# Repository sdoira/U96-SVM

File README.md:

# U96-SVM
Stereo vision front-end for Ultra96v2

## About
U96-SVM is an add-on board for Avnet Ultra96v2.
This board has dual CMOS image sensors and two mikroBUS sites.
This repository contains all design files for the hardware and a sample project 
which transfers stereo images through a USB interface.

## Tools

These tools are used to create this project.
1. Avnet Ultra96v2
2. Autodesk EAGLE 9.6.2
3. Xilinx Vivado 2020.1
4. Xilinx Vitis 2020.1

## PCB
This PCB is designed to be compliant with 96Boards specifications.
The number of layers is 4.
The minimum trace width and minimum drill diameter are 0.15mm and 0.25mm respectively.
This design rule is according to EuroCircuits 6D class.

EAGLE 9.6.2 is used in designing PCB.
This project doesn't contain Gerber files. EAGLE board layout file (.brd) is directly used to order manufacturing.
If you want to place an order simply upload the BRD file to the EuroCircuits website.
The assembly service is also possible by enabling the "Include assembly" option then upload the BOM file.

## USB Interface
This device is recognized as USB Video Class (UVC) device when connected to the host PC.
The sample project supports the following resolution both for USB2.0 and USB3.0.

| USB Ver. | Single Image Resolution | FPS  |
| :---     | :---                    | :--- |
| 2.0      | 640 x 480               | 30   |
| 3.0      | 640 x 480               | 30   |

The left and right images are combined horizontally.
The actual output image is twice wide.

## Vivado Project
This repository contains 2 Vivado projects.
One of them is the Vivado top level project.
The other is a project for a user-created IP module.
Both of them can be created by running TCL scripts.
Refer to "create_project_dvp.pdf" and "create_project1.pdf" about how to create these projects.

## Vitis Project
The Vitis project contains a sample application named "usb_grabber".
This application, when launched, automatically starts DMA transferring of stereo images while waiting for a USB connection.
Refer to "create_vitis_project.pdf" about how to create the Vitis project.

## License
### Hardware
The hardware documentation and products included in this repository are licensed under the TAPR Open Hardware License (www.tapr.org/OHL).
The hardware documentation is contained in the following directory.

	/eagle/

### Software
The software design files included in this repository are available under the MIT license.
Such design files are contained in the following directories.

	/src/dvp/rtl/		--- Verilog-HDL RTL source
	/src/dvp/sim/		--- Verilog-HDL simulation test bench
	/src/usb_grabber/	--- C source

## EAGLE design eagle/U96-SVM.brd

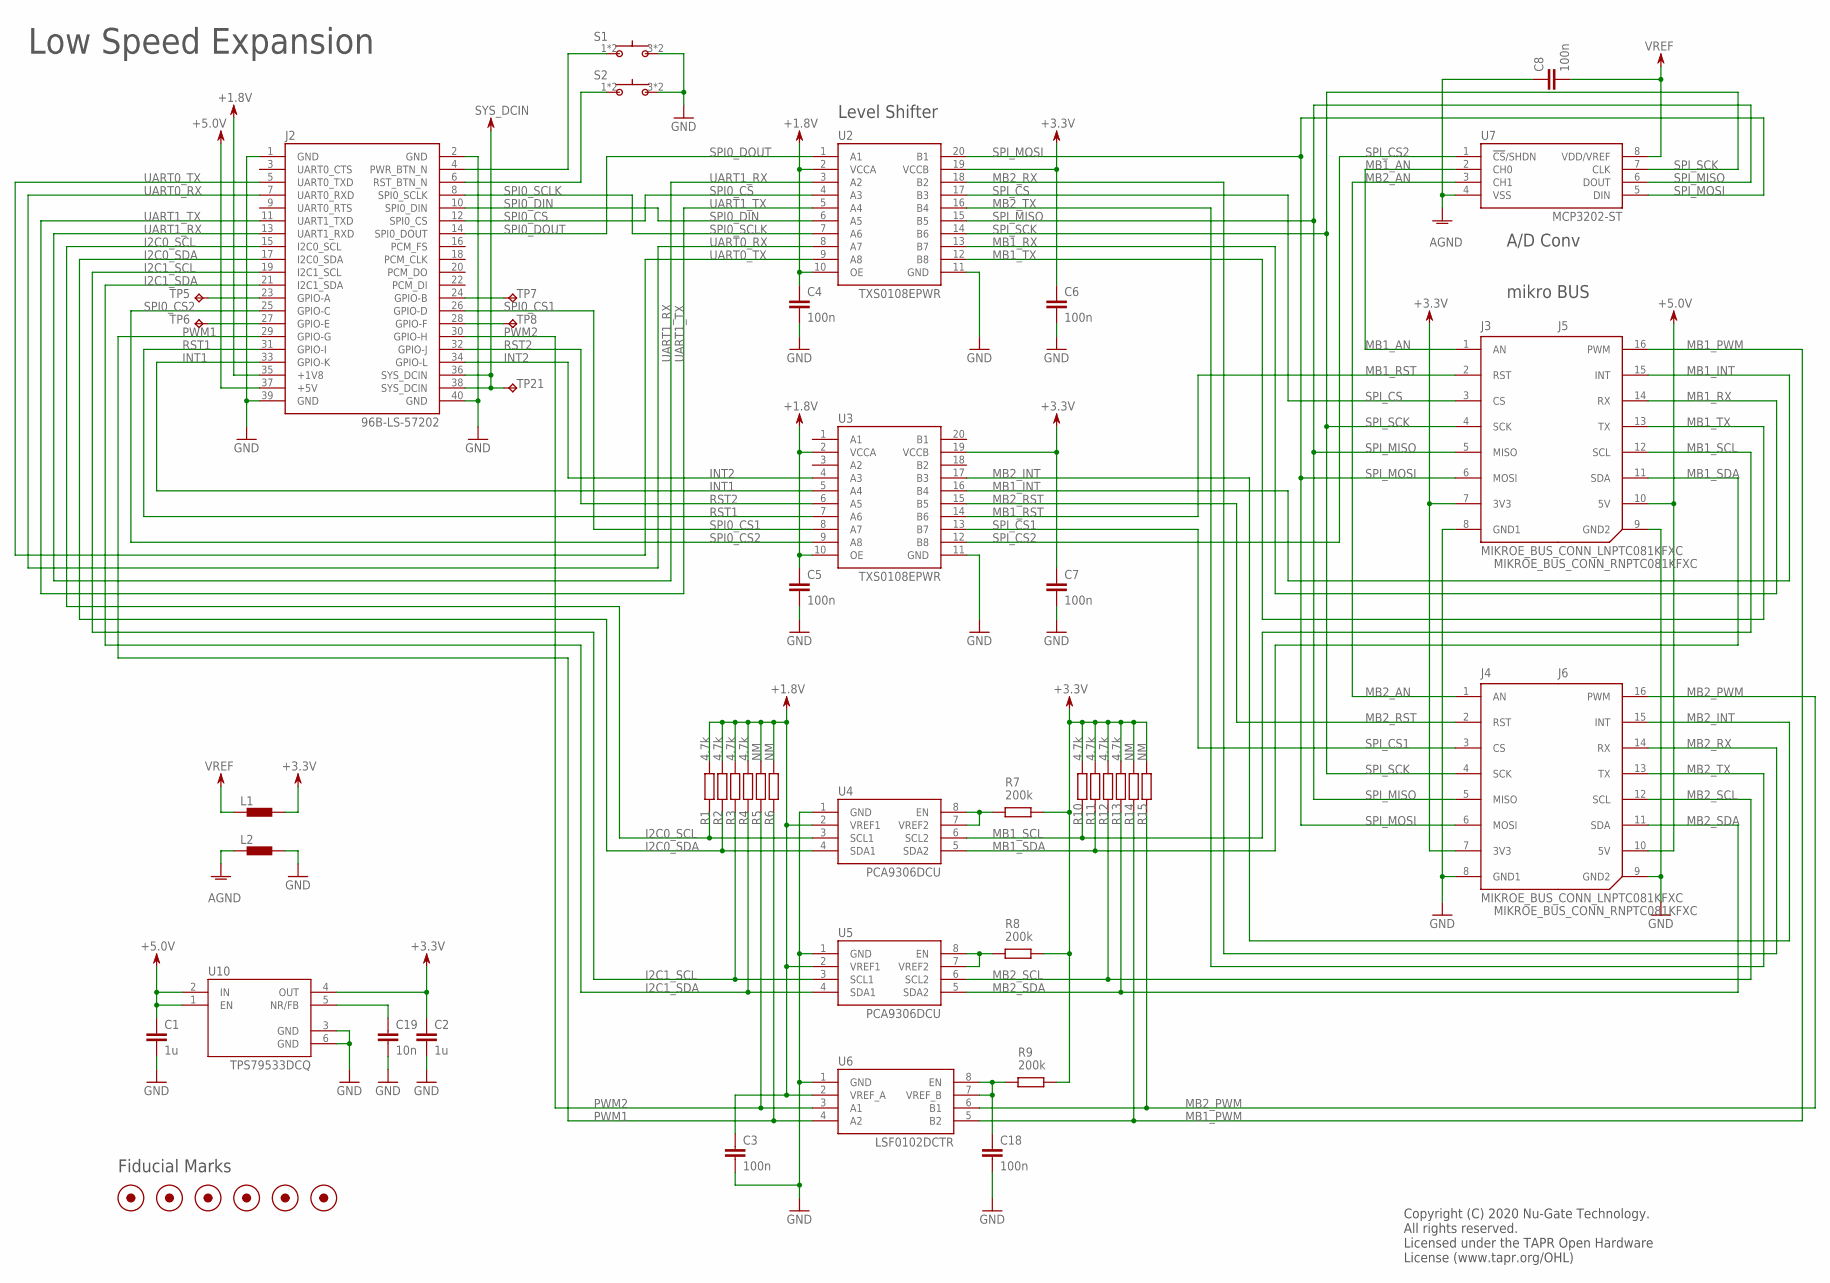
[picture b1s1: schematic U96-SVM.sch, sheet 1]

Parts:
C1, C2: 1u; C0402
C3, C4, C5, C6, C7, C8, C18: 100n; C0402
C19: 10n; C0402
FID1, FID2, FID3, FID4, FID5, FID6: FIDUCIAL; FIDUCIAL_1MM
J2: 96B-LS-57202; 57202-G52-20LF
J3, J4: MIKROE_BUS_CONN_LNPTC081KFXC; MIKROBUS_HOST_CONN_L2
J5, J6: MIKROE_BUS_CONN_RNPTC081KFXC; MIKROBUS_HOST_CONN_R2
L1, L2: BLM15AX; 0402
R1, R2, R3, R4, R10, R11, R12, R13: 4.7k; R0402
R5, R6, R14, R15: NM; R0402
R7, R8, R9: 200k; R0402
S1, S2: 430181038816
TP5, TP6, TP7, TP8, TP21: TPB1,27; B1,27
U2, U3: TXS0108EPWR; TI-PW20
U4, U5: PCA9306DCU; TI-DCU8
U6: LSF0102DCTR; TI-DCT8
U7: MCP3202-ST; MC-ST8
U10: TPS79533DCQ; TI-SOT223

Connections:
+1.8V: C3.1, C4.1, C5.1, J2.35 (+1V8), R1.2, R2.2, R3.2, R4.2, R5.2, R6.2, U2.2 (VCCA), U2.10 (OE), U3.2 (VCCA), U3.10 (OE), U4.2 (VREF1), U5.2 (VREF1), U6.2 (VREF_A); also elsewhere on the board
+3.3V: C2.1, C6.1, C7.1, J3.7 (3V3), J4.7 (3V3), L1.2, R7.2, R8.2, R9.2, R10.2, R11.2, R12.2, R13.2, R14.2, R15.2, U2.19 (VCCB), U3.19 (VCCB), U10.4 (OUT); also elsewhere on the board
+5.0V: C1.1, J2.37 (+5V), J5.10 (5V), J6.10 (5V), U10.1 (EN), U10.2 (IN); also elsewhere on the board
AGND: C8.1, L2.1, U7.4 (VSS)
GND: C1.2, C2.2, C3.2, C4.2, C5.2, C6.2, C7.2, C18.2, C19.2, J2.1 (GND), J2.2 (GND), J2.39 (GND), J2.40 (GND), J3.8 (GND1), J4.8 (GND1), J5.9 (GND2), J6.9 (GND2), L2.2, S1.3, S1.4, S2.3, S2.4, U2.11 (GND), U3.11 (GND), U4.1 (GND), U5.1 (GND), U6.1 (GND), U10.3 (GND), U10.6 (GND); also elsewhere on the board
I2C0_SCL: J2.15 (I2C0_SCL), R1.1, U4.3 (SCL1)
I2C0_SDA: J2.17 (I2C0_SDA), R2.1, U4.4 (SDA1)
I2C1_SCL: J2.19 (I2C1_SCL), R3.1, U5.3 (SCL1)
I2C1_SDA: J2.21 (I2C1_SDA), R4.1, U5.4 (SDA1)
INT1: J2.33 (GPIO-K), U3.5 (A4)
INT2: J2.34 (GPIO-L), U3.4 (A3)
MB1_AN: J3.1 (AN), U7.2 (CH0)
MB1_INT: J5.15 (INT), U3.16 (B4)
MB1_PWM: J5.16 (PWM), R14.1, U6.5 (B2)
MB1_RST: J3.2 (RST), U3.14 (B6)
MB1_RX: J5.14 (RX), U2.13 (B7)
MB1_SCL: J5.12 (SCL), R10.1, U4.6 (SCL2)
MB1_SDA: J5.11 (SDA), R11.1, U4.5 (SDA2)
MB1_TX: J5.13 (TX), U2.12 (B8)
MB2_AN: J4.1 (AN), U7.3 (CH1)
MB2_INT: J6.15 (INT), U3.17 (B3)
MB2_PWM: J6.16 (PWM), R15.1, U6.6 (B1)
MB2_RST: J4.2 (RST), U3.15 (B5)
MB2_RX: J6.14 (RX), U2.18 (B2)
MB2_SCL: J6.12 (SCL), R12.1, U5.6 (SCL2)
MB2_SDA: J6.11 (SDA), R13.1, U5.5 (SDA2)
MB2_TX: J6.13 (TX), U2.16 (B4)
unnamed: R7.1, U4.7 (VREF2), U4.8 (EN)
unnamed: C18.1, R9.1, U6.7 (VREF_B), U6.8 (EN)
unnamed: R8.1, U5.7 (VREF2), U5.8 (EN)
unnamed: C19.1, U10.5 (NR/FB)
unnamed: J2.23 (GPIO-A), TP5.TP
unnamed: J2.4 (PWR_BTN_N), S1.1, S1.2
unnamed: J2.6 (RST_BTN_N), S2.1, S2.2
unnamed: J2.27 (GPIO-E), TP6.TP
unnamed: J2.24 (GPIO-B), TP7.TP
unnamed: J2.28 (GPIO-F), TP8.TP
PWM1: J2.29 (GPIO-G), R6.1, U6.4 (A2)
PWM2: J2.30 (GPIO-H), R5.1, U6.3 (A1)
RST1: J2.31 (GPIO-I), U3.7 (A6)
RST2: J2.32 (GPIO-J), U3.6 (A5)
SPI0_CS: J2.12 (SPI0_CS), U2.4 (A3)
SPI0_CS1: J2.26 (GPIO-D), U3.8 (A7)
SPI0_CS2: J2.25 (GPIO-C), U3.9 (A8)
SPI0_DIN: J2.10 (SPI0_DIN), U2.6 (A5)
SPI0_DOUT: J2.14 (SPI0_DOUT), U2.1 (A1)
SPI0_SCLK: J2.8 (SPI0_SCLK), U2.7 (A6)
SPI_CS: J3.3 (CS), U2.17 (B3)
SPI_CS1: J4.3 (CS), U3.13 (B7)
SPI_CS2: U3.12 (B8), U7.1 (!CS!/SHDN)
SPI_MISO: J3.5 (MISO), J4.5 (MISO), U2.15 (B5), U7.6 (DOUT)
SPI_MOSI: J3.6 (MOSI), J4.6 (MOSI), U2.20 (B1), U7.5 (DIN)
SPI_SCK: J3.4 (SCK), J4.4 (SCK), U2.14 (B6), U7.7 (CLK)
SYS_DCIN: J2.36 (SYS_DCIN), J2.38 (SYS_DCIN), TP21.TP
UART0_RX: J2.7 (UART0_RXD), U2.8 (A7)
UART0_TX: J2.5 (UART0_TXD), U2.9 (A8)
UART1_RX: J2.13 (UART1_RXD), U2.3 (A2)
UART1_TX: J2.11 (UART1_TXD), U2.5 (A4)
VREF: C8.2, L1.1, U7.8 (VDD/VREF)

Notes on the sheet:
Fiducial Marks
Low Speed Expansion
Level Shifter
mikro BUS
A/D Conv
Copyright (C) 2020 Nu-Gate Technology. All rights reserved. Licensed under the TAPR Open Hardware License (www.tapr.org/OHL)

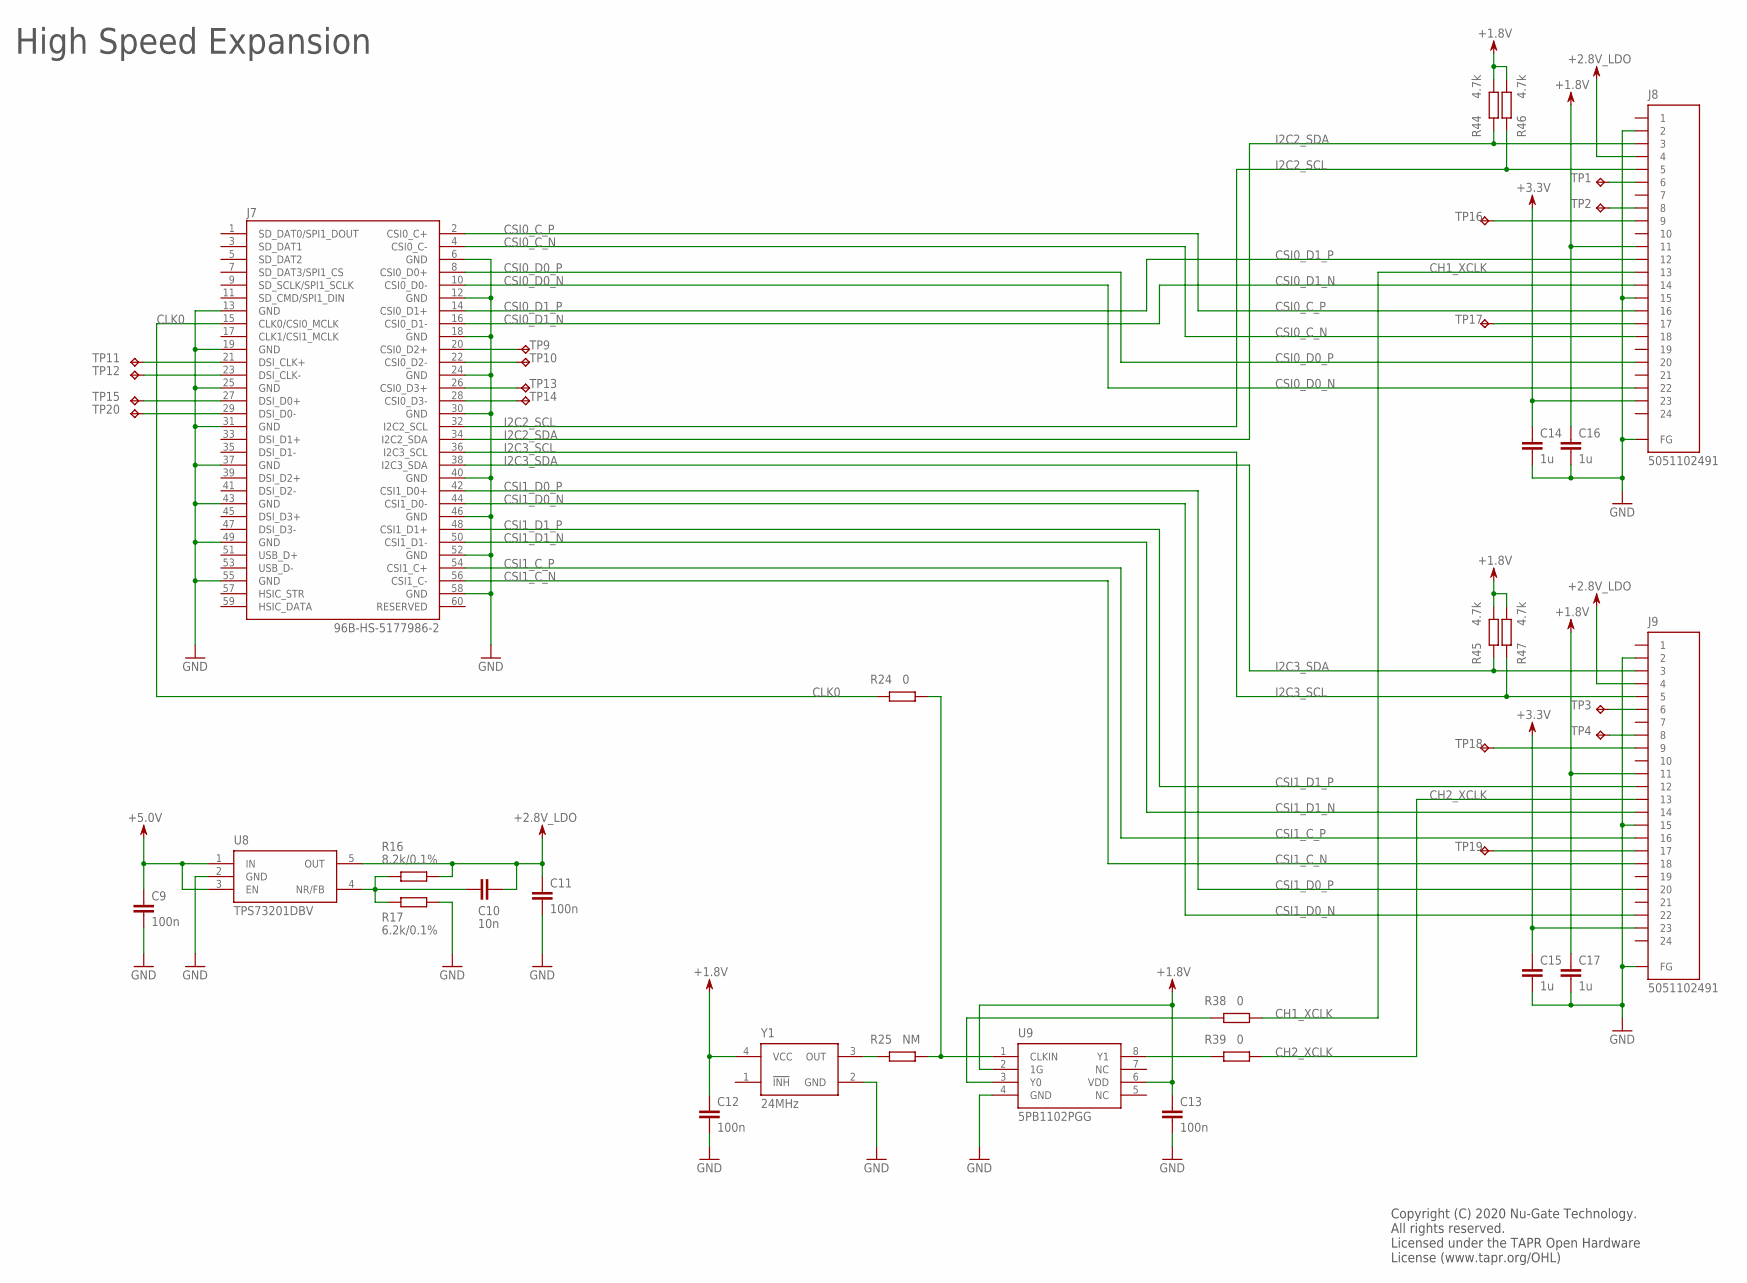
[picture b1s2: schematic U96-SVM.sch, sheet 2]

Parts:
C9, C11, C12, C13: 100n; C0402
C10: 10n; C0402
C14, C15, C16, C17: 1u; C0402
J7: 96B-HS-5177986-2; 5177986-2
J8, J9: 5051102491; MO-5051102491
R16: 8.2k/0.1%; R0402
R17: 6.2k/0.1%; R0402
R24, R38, R39: 0; R0402
R25: NM; R0402
R44, R45, R46, R47: 4.7k; R0402
TP1, TP2, TP3, TP4, TP9, TP10, TP11, TP12, TP13, TP14, TP15, TP16, TP17, TP18, TP19, TP20: TPB1,27; B1,27
U8: TPS73201DBV; TI-SOT23
U9: 5PB1102PGG; ID-TSSOP8
Y1: 24MHz; KC2520Z

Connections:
+1.8V: C12.1, C13.1, C16.1, C17.1, J8.11, J9.11, R44.2, R45.2, R46.2, R47.2, U9.2 (1G), U9.6 (VDD), Y1.4 (VCC); also elsewhere on the board
+2.8V_LDO: C10.2, C11.1, J8.4, J9.4, R16.2, U8.5 (OUT)
+3.3V: C14.1, C15.1, J8.23, J9.23; also elsewhere on the board
+5.0V: C9.1, U8.1 (IN), U8.3 (EN); also elsewhere on the board
CH1_XCLK: J8.13, R38.2
CH2_XCLK: J9.13, R39.2
CLK0: J7.15 (CLK0/CSI0_MCLK), R24.1
CSI0_C_N: J7.4 (CSI0_C-), J8.18
CSI0_C_P: J7.2 (CSI0_C+), J8.16
CSI0_D0_N: J7.10 (CSI0_D0-), J8.22
CSI0_D0_P: J7.8 (CSI0_D0+), J8.20
CSI0_D1_N: J7.16 (CSI0_D1-), J8.14
CSI0_D1_P: J7.14 (CSI0_D1+), J8.12
CSI1_C_N: J7.56 (CSI1_C-), J9.18
CSI1_C_P: J7.54 (CSI1_C+), J9.16
CSI1_D0_N: J7.44 (CSI1_D0-), J9.22
CSI1_D0_P: J7.42 (CSI1_D0+), J9.20
CSI1_D1_N: J7.50 (CSI1_D1-), J9.14
CSI1_D1_P: J7.48 (CSI1_D1+), J9.12
GND: C9.2, C11.2, C12.2, C13.2, C14.2, C15.2, C16.2, C17.2, J7.6 (GND), J7.12 (GND), J7.13 (GND), J7.18 (GND), J7.19 (GND), J7.24 (GND), J7.25 (GND), J7.30 (GND), J7.31 (GND), J7.37 (GND), J7.40 (GND), J7.43 (GND), J7.46 (GND), J7.49 (GND), J7.52 (GND), J7.55 (GND), J7.58 (GND), J8.2, J8.15, J8.FG@1 (FG), J8.FG@2 (FG), J9.2, J9.15, J9.FG@1 (FG), J9.FG@2 (FG), R17.2, U8.2 (GND), U9.4 (GND), Y1.2 (GND); also elsewhere on the board
I2C2_SCL: J7.32 (I2C2_SCL), J8.5, R46.1
I2C2_SDA: J7.34 (I2C2_SDA), J8.3, R44.1
I2C3_SCL: J7.36 (I2C3_SCL), J9.5, R47.1
I2C3_SDA: J7.38 (I2C3_SDA), J9.3, R45.1
unnamed: J8.6, TP1.TP
unnamed: J8.8, TP2.TP
unnamed: J9.6, TP3.TP
unnamed: J9.8, TP4.TP
unnamed: C10.1, R16.1, R17.1, U8.4 (NR/FB)
unnamed: J7.21 (DSI_CLK+), TP11.TP
unnamed: J7.23 (DSI_CLK-), TP12.TP
unnamed: J7.27 (DSI_D0+), TP15.TP
unnamed: J7.29 (DSI_D0-), TP20.TP
unnamed: J7.20 (CSI0_D2+), TP9.TP
unnamed: J7.22 (CSI0_D2-), TP10.TP
unnamed: J7.26 (CSI0_D3+), TP13.TP
unnamed: J7.28 (CSI0_D3-), TP14.TP
unnamed: R25.1, Y1.3 (OUT)
unnamed: R24.2, R25.2, U9.1 (CLKIN)
unnamed: R39.1, U9.8 (Y1)
unnamed: R38.1, U9.3 (Y0)
unnamed: J8.9, TP16.TP
unnamed: J8.17, TP17.TP
unnamed: J9.9, TP18.TP
unnamed: J9.17, TP19.TP

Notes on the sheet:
High Speed Expansion
Copyright (C) 2020 Nu-Gate Technology. All rights reserved. Licensed under the TAPR Open Hardware License (www.tapr.org/OHL)

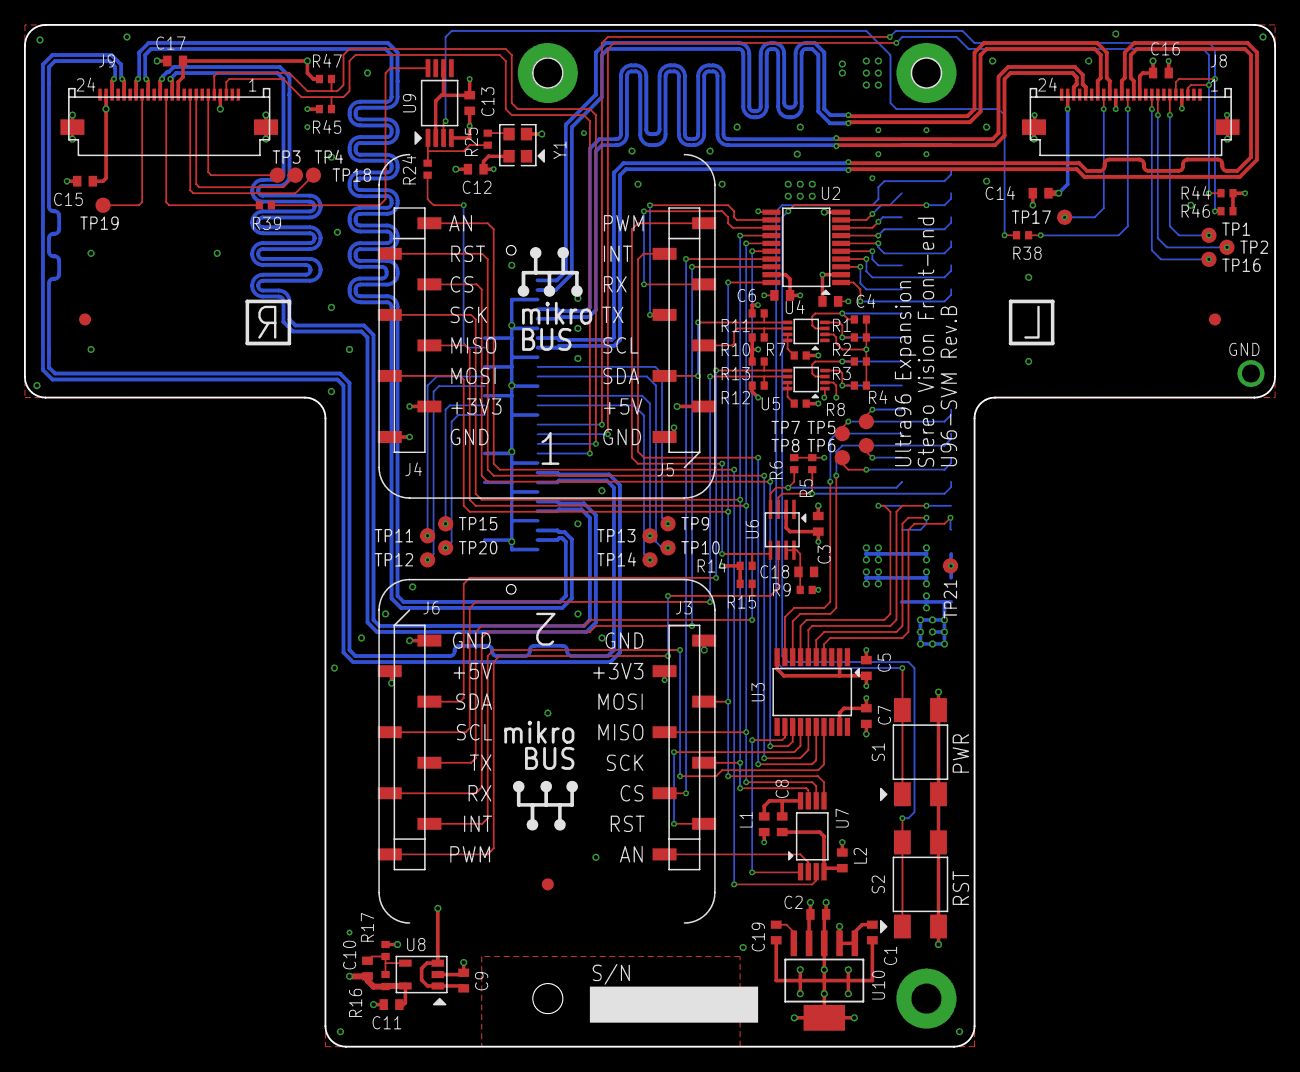
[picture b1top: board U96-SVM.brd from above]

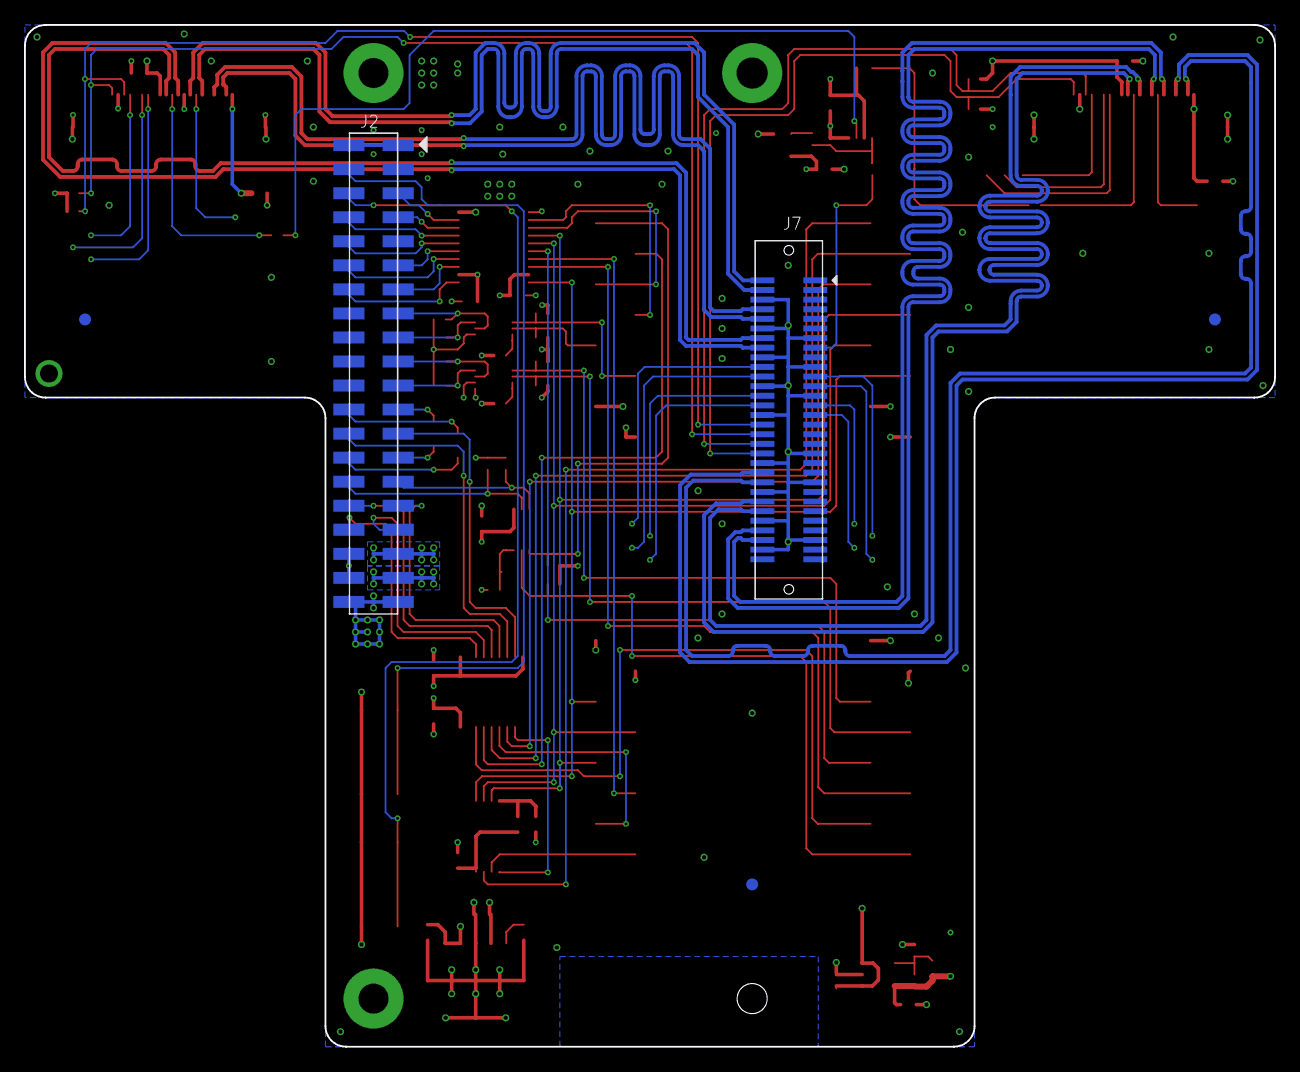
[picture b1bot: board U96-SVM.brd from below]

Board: 4 copper layers, 104.0 x 85.0 mm, 100 parts (5 on the bottom side), 100 nets.

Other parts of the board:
U$1: 96BOARDS_FORM_FACTOR
U$2, U$3: FD5640-500W
U$4, U$7: MIKROBUS_LOGO1
U$5, U$6: MIKROBUS_LOGO2

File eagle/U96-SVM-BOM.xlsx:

Qty | Value | Device | Parts | Description | Manufacturer | MPN | Supplier | SPN
6 | 1u | C-EUC0402 | C1, C2, C14, C15, C16, C17 | CAP CER 1UF 10V X5R 0603 | Murata | GRM188R61A105KA61J | Digi-Key | 490-6408-1-ND
2 | 10n | C-EUC0402 | C10, C19 | CAP CER 10000PF 50V C0G/NP0 0603 | Murata | GRM1885C1H103JA01D | Digi-Key | 490-9666-1-ND
11 | 100n | C-EUC0402 | C3, C4, C5, C6, C7, C8, C9, C11, C12, C13, C18 | CAP CER 0.1UF 10V X5R 0402 | Murata | GRM155R61A104KA01J | Digi-Key | 490-6297-1-ND
6 |  | FIDUCIAL | FID1, FID2, FID3, FID4, FID5, FID6 | Fiducial marks, 1mm | - | - | - | -
1 | 96B-LS-57202 | 96B-LS-57202 | J2 | CONN HEADER SMD 40POS 2MM | Amphenol | 57202-G52-20LF | Digi-Key | 609-2632-ND
2 | MIKROE_BUS_CONN_LNPTC081KFXC | MIKROE_BUS_CONN_LNPTC081KFXC | J3, J4 | CONN HDR 8POS 0.1 TIN SMD | Sullins | NPTC081KFXC-RC | Digi-Key | S5600-ND
2 | MIKROE_BUS_CONN_RNPTC081KFXC | MIKROE_BUS_CONN_RNPTC081KFXC | J5, J6 | CONN HDR 8POS 0.1 TIN SMD | Sullins | NPTC081KFXC-RC | Digi-Key | S5600-ND
1 | 96B-HS-5177986-2 | 96B-HS-5177986-2 | J7 | CONN PLUG 60POS SMD GOLD | TE | 2-5177986-2 | Digi-Key | A99209CT-ND
2 | 5051102491 | 5051102491 | J8, J9 | CONN FFC/FPC BOTTOM 24P .5MM R/A | Molex | 5051102491 | Digi-Key | WM11289CT-ND
2 |  | BLM15AX | L1, L2 | FERRITE BEAD 220 OHM 0603 1LN | Murata | BLM18AG221SN1D | Digi-Key | 490-1012-1-ND
12 | 4.7k | R-EU_R0402 | R1, R2, R3, R4, R10, R11, R12, R13, R44, R45, R46, R47 | RES SMD 4.7K OHM 5% 1/16W 0402 | Yageo | RC0402JR-074K7L | Digi-Key | 311-4.7KJRCT-ND
1 | 8.2k/0.1% | R-EU_R0402 | R16 | RES SMD 8.2K OHM 0.1% 1/16W 0402 | Yageo | RT0402BRD078K2L | Digi-Key | YAG4318CT-ND
1 | 6.2k/0.1% | R-EU_R0402 | R17 | RES SMD 6.2K OHM 0.1% 1/16W 0402 | Yageo | RT0402BRD076K2L | Digi-Key | YAG4302CT-ND
3 | 0 | R-EU_R0402 | R24, R38, R39 | RES SMD 0 OHM JUMPER 1/16W 0402 | Yageo | RC0402JR-070RL | Digi-Key | 311-0.0JRCT-ND
5 | NM | R-EU_R0402 | R5, R6, R14, R15, R25 | No Mount | - | - | - | -
3 | 200k | R-EU_R0402 | R7, R8, R9 | RES SMD 200K OHM 5% 1/16W 0402 | Yageo | RC0402JR-07200KL | Digi-Key | 311-200KJRCT-ND
2 | 430181038816 | 430181038816 | S1, S2 | SWITCH TACTILE SPST-NO 0.05A 12V | Wurth | 430181038816 | Digi-Key | 732-7003-1-ND
20 | TPB1,27 | TPB1,27 | TP1, TP2, TP3, TP4, TP5, TP6, TP7, TP8, TP9, TP10, TP11, TP12, TP13, TP14, TP15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 | Test pad | - | - | - | -
1 | TPS79533DCQ | TPS79533DCQ | U10 | IC REG LIN 3.3V 500MA SOT223-6 | TI | TPS79533DCQR | Digi-Key | 296-13810-1-ND
2 | TXS0108EPWR | TXS0108EPWR | U2, U3 | IC TRNSLTR BIDIRECTIONAL 20TSSOP | TI | TXS0108EPWR | Digi-Key | 296-23011-1-ND
2 | PCA9306DCU | PCA9306DCU | U4, U5 | IC TRNSLTR BIDIRECTIONAL 8VSSOP | TI | PCA9306DCUR | Digi-Key | 296-17988-1-ND
1 | LSF0102DCTR | LSF0102DCTR | U6 | IC TRNSLTR BIDIRECTIONAL SM8 | TI | LSF0102DCTR | Digi-Key | 296-40398-1-ND
1 | MCP3202-ST | MCP3202-ST | U7 | IC ADC 12BIT SAR 8TSSOP | Microchip | MCP3202T-CI/ST | Digi-Key | MCP3202T-CI/STCT-ND
1 | TPS73201DBV | TPS73201DBV | U8 | IC REG LIN POS ADJ 250MA SOT23-5 | TI | TPS73201DBVR | Digi-Key | 296-32554-1-ND
1 | 5PB1102PGG | 5PB1102PGG | U9 | IC CLOCK BUFFER 1:2 8TSSOP | Renesas | 5PB1102PGGI | Digi-Key | 800-2889-5-ND
1 | 24MHz | KC2520Z | Y1 | XTAL OSC XO 24.0000MHZ CMOS SMD | Kyocera | KC2520Z24.0000C1KX00 | Digi-Key | 1253-2019-1-ND
 | Copyright (C) 2020 Nu-Gate Technology. All rights reserved.
 | Licensed under the TAPR Open Hardware License (www.tapr.org/OHL)

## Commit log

2020-12-10 specify hardware documentation directory
2020-12-10 typo
2020-12-10 usb version
2020-12-12 modified USB VID/PID
